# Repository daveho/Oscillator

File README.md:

# Oscillator PCB

This project started because I needed a 10 MHz oscillator that could run with
VCC at 3.3V to provide a clock signal to a 3.3V FPGA. I do have some
10 MHz full-can oscillators, but I don't have a datasheet for them, and
it's not clear whether they are rated to run at 3.3V. So, I designed a
small PCB with the same pinout as a full-can oscillator which
uses a surface mount 74HC04 and a low-profile HC-49US through-hole crystal
to generate a 10 MHz square wave.

The schematic and PCB design were (of course!) created using [KiCad](https://www.kicad.org/).

Obligatory photo:

The assembled module is *approximately* the same size as a standard full-can oscillator,
and has the same pin spacing. Note that unlike a "real" oscillator,
pin 1 isn't an input that you can ground to disable the clock
output, so if you need that functionality, this module won't work.

It produces a reasonable 10 MHz square wave:

Parts list:

Symbol | Part | Note
------ | ---- | ----
R1 | 1 MΩ 0805 resistor |
R2 | 1 kΩ 0805 resistor |
C1 | 100 nF 0805 capacitor | decoupling for the 74HC04
C2, C3 | 22 pF 0805 capacitor | loading caps
U1 | 74HC04 in a TSSOP-14 package | inverters for oscillator, output
Y1 | 10 MHz HC-49US low-profile crystal | parallel resonance (not series)
J1–J4 | Male header pins | whatever kind you prefer, I like the round ones

The resistors and capacitors are 0805 package (imperial measurement).
I got most of the components from [LCSC](https://www.lcsc.com/).
The boards were fabbed by [OSHPark](https://www.oshpark.com/).
(You can just upload [Oscillator.kicad\_pcb](Oscillator.kicad_pcb)
to OSHPark, no need to generate Gerbers, drill files, and whatnot.)

The circuit will likely work with other crystal frequencies
(I think you would just need to select loading capacitors appropriately.)

I'm not particularly skilled at surface mount soldering, but I had no
trouble assembling these. I used drag soldering with lots of flux gel for
the 74HC04, with only tiny amounts of solder on the tip of the iron.
For the resistors and capacitors, I melted solder onto one pad,
used tweezers to position the component (with the solder melted),
then soldered the other pad.

## License

This board is made available as public domain (CC0). I provide no guarantee that
it will do anything useful: use it at your own risk.

<p xmlns:cc="http://creativecommons.org/ns#" xmlns:dct="http://purl.org/dc/terms/"><a property="dct:title" rel="cc:attributionURL" href="https://github.com/daveho/Oscillator">Oscillator PCB</a> by <a rel="cc:attributionURL dct:creator" property="cc:attributionName" href="https://daveho.github.io/">David Hovemeyer</a> is marked with <a href="http://creativecommons.org/publicdomain/zero/1.0?ref=chooser-v1" target="_blank" rel="license noopener noreferrer" style="display:inline-block;">CC0 1.0</a></p>

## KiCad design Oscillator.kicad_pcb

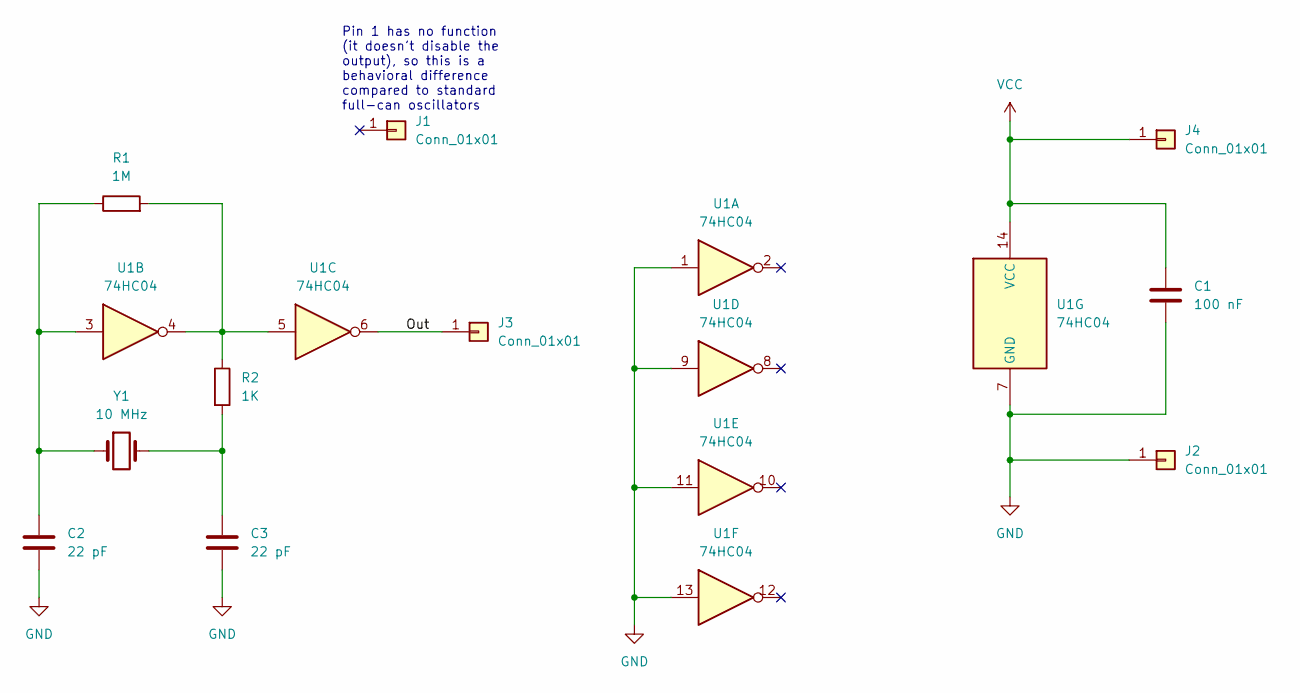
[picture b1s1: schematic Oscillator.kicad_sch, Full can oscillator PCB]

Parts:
C1: 100 nF; C_0805_2012Metric
C2, C3: 22 pF; C_0805_2012Metric
J1, J2, J3, J4: Conn_01x01; PinHeader_1x01_P2.54mm_Vertical
R1: 1M; R_0805_2012Metric
R2: 1K; R_0805_2012Metric
U1: 74HC04; TSSOP-14_4.4x5mm_P0.65mm
Y1: 10 MHz; Crystal_HC49-U_Vertical

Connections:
/Out: J3.1, U1.6
GND: C1.2, C2.2, C3.2, J2.1, U1.1, U1.7 (GND), U1.9, U1.11, U1.13
unnamed: C2.1, R1.1, U1.3, Y1.1
unnamed: C3.1, R2.2, Y1.2
unnamed: R1.2, R2.1, U1.4, U1.5
VCC: C1.1, J4.1, U1.14 (VCC)

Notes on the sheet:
Pin 1 has no function (it doesn't disable the output), so this is a behavioral difference compared to standard full-can oscillators

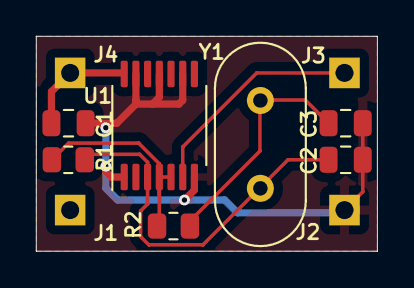
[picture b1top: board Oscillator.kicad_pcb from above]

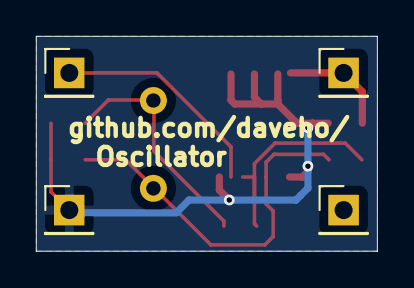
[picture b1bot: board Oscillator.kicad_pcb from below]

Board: 2 copper layers, 18.9 x 11.9 mm, 11 parts (4 on the bottom side), 6 nets.

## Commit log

2023-11-26 routed all signals
2023-12-13 silkscreen improvements
2023-12-13 board works, added a README.md
2023-12-13 minor tweak to README.md
2023-12-13 one more minor tweak
